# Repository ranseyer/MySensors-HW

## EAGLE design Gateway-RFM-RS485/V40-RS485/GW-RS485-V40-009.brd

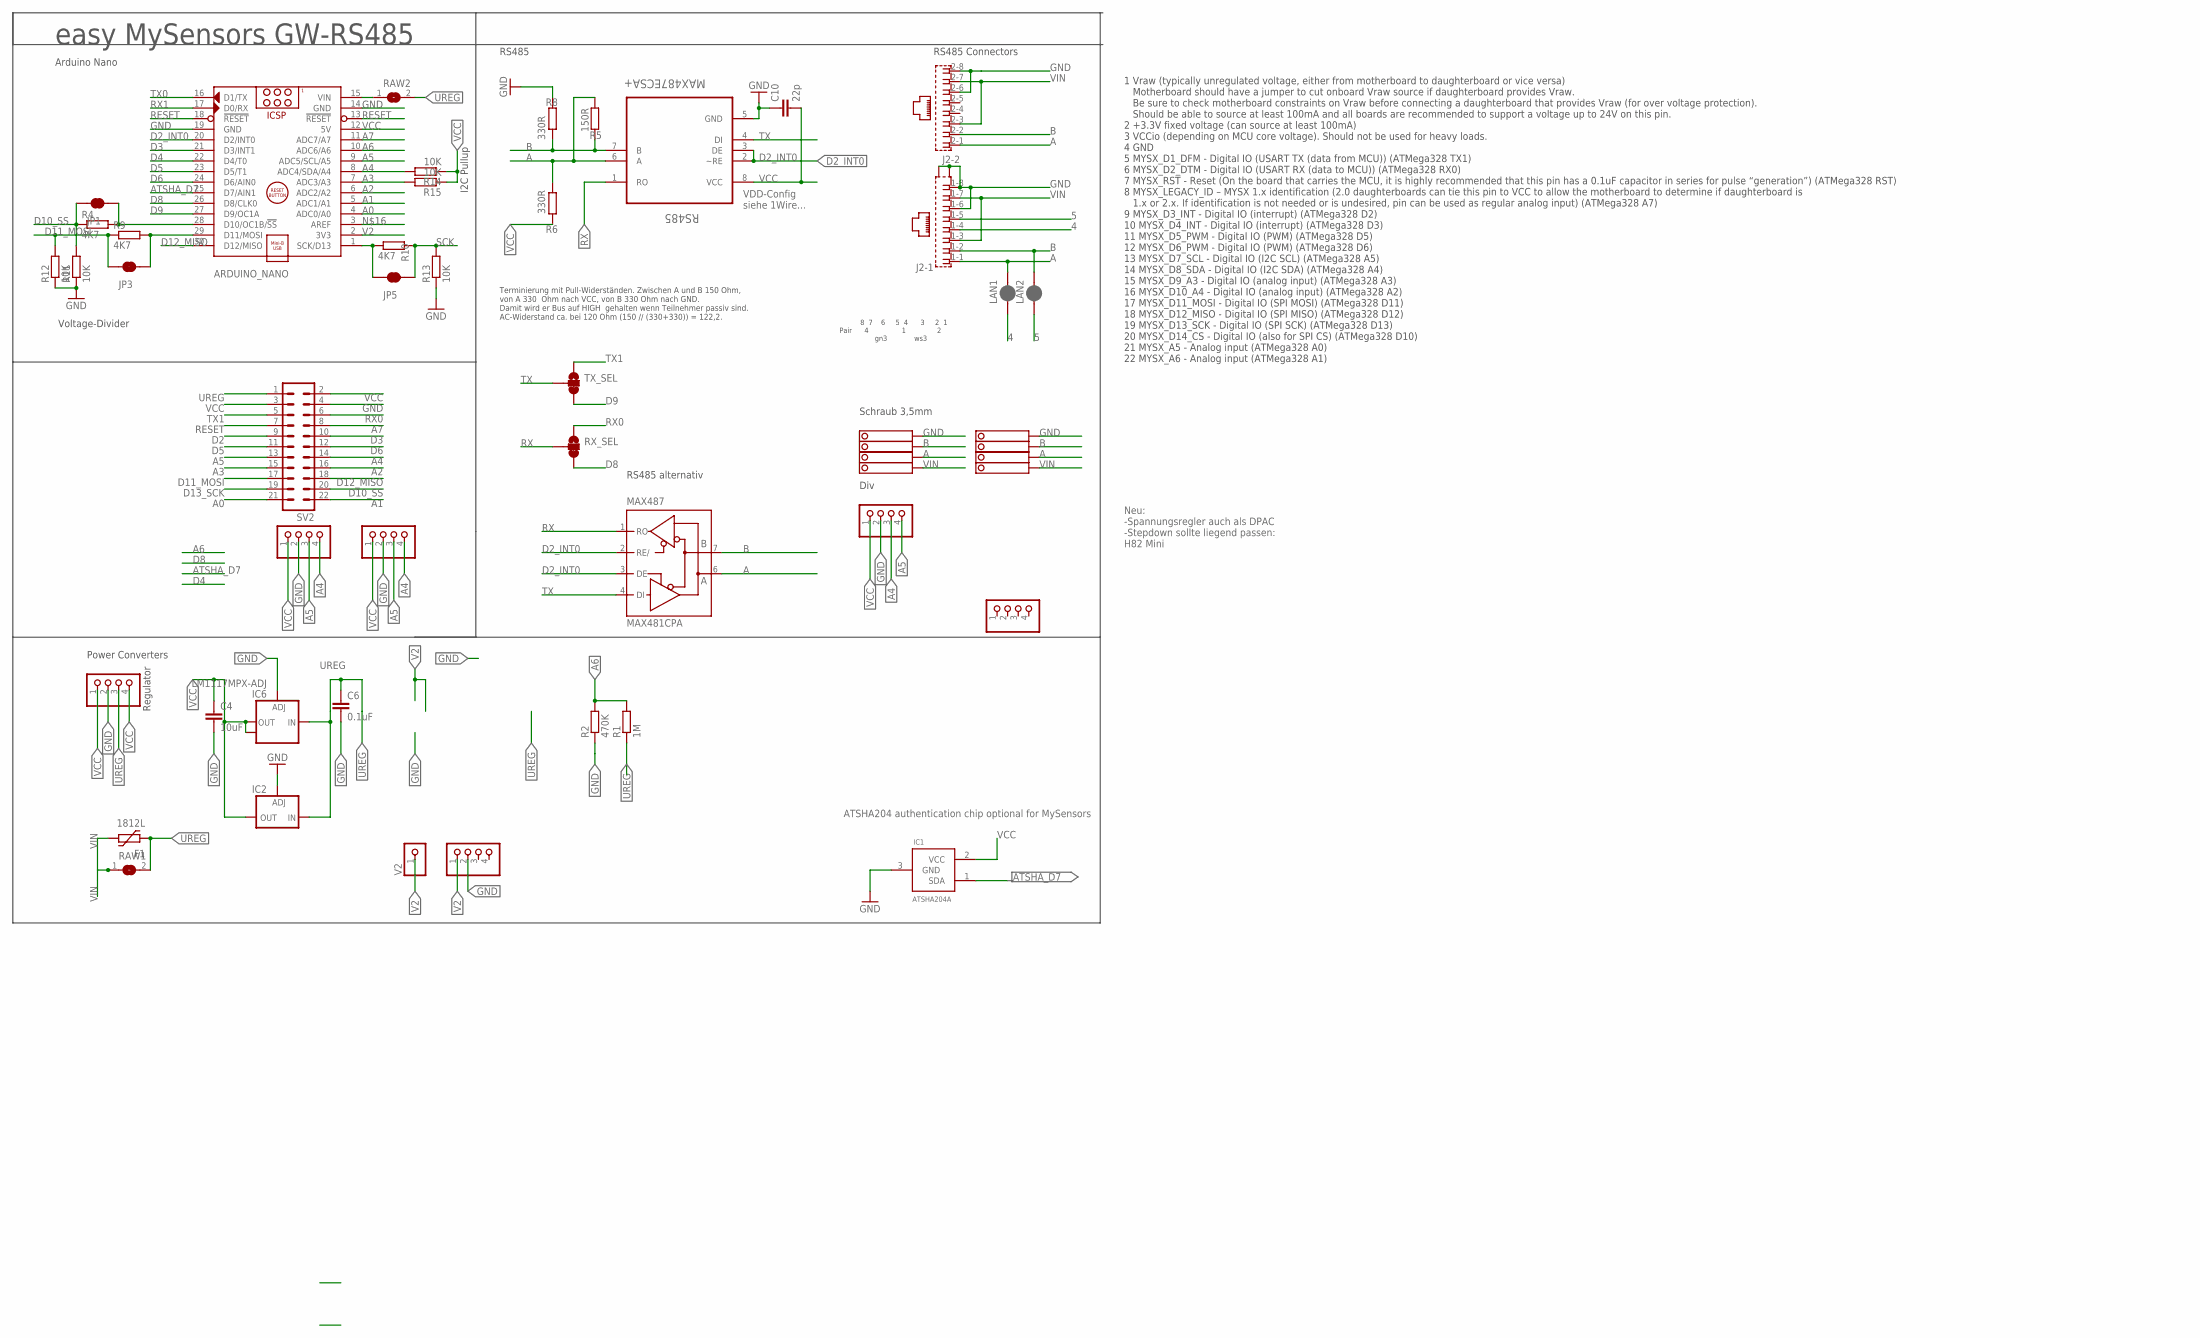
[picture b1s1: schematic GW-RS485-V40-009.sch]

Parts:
ARDUINO_NANO: ARDUINO_NANO_OHNE-BOHR; ARDUINO_NANO
BH1750: PINHD-1X04_2.54-S; 1X04-S
C4: 10uF; C1210
C6: 0.1uF; C1206
C10: 22p; C0805
F1: 1812L
I2C-1, I2C-2: PINHD-1X04_2.54-S; 1X04-S
IC1: ATSHA204A; SOT23
IC2: LD117ADT50TR; DPACK
IC6: LM1117MPX-ADJ; SOT223
J2: RJ45_2X_NARROW_SHILDPINS_NOCASE
JP1, JP3, JP5: JUMPER-SMT_2_NC_TRACE_SILK; SMT-JUMPER_2_NC_TRACE_SILK
JP2: PINHD-1X04_2.54-S; 1X04-S
LAN1, LAN2: JUMPER-SMT_2_NC_PASTE_SILK; SMT-JUMPER_2_NC_PASTE_SILK
MAX487: MAX481CPA; DIL08
R1: 1M; R0805
R2: 470K; R0805
R4, R9, R10: 4K7; M0805
R5: 150R; R0805
R6, R8: 330R; R0805
R11, R12, R13: 10K; M0805
R14, R15: 10K; R0805
RAW1, RAW2: SJ
RS485: MAX487ECSA+; SOIC127P600X175-8N
RX_SEL: JUMPER-SMT_3_1-NC_TRACE_SILK; SMT-JUMPER_3_1-NC_TRACE_SILK
STEPDWN: PINHD-1X04_2.54-S; 1X04-S
SV2: MA11-2
TX_SEL: JUMPER-SMT_3_1-NC_TRACE_SILK; SMT-JUMPER_3_1-NC_TRACE_SILK
V2: PINHD-1X1; 1X01
V2-: PINHD-1X04_2.54-S; 1X04-S
X1, X4: 1751264

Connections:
4: J2.1-4 (4), LAN1.1
5: J2.1-5 (5), LAN2.1
A: J2.1-1 (1), J2.2-1 (1), LAN1.2, MAX487.6 (A), R5.1, R6.2, RS485.6 (A), X1.2, X4.2
A0: ARDUINO_NANO.4 (ADC0/A0), SV2.21
A1: ARDUINO_NANO.5 (ADC1/A1), SV2.22
A2: ARDUINO_NANO.6 (ADC2/A2), SV2.16
A3: ARDUINO_NANO.7 (ADC3/A3), R15.2, SV2.15
A4: ARDUINO_NANO.8 (ADC4/SDA/A4), BH1750.4, I2C-1.4, I2C-2.3, R14.2, SV2.14
A5: ARDUINO_NANO.9 (ADC5/SCL/A5), BH1750.3, I2C-1.3, I2C-2.4, SV2.13
A6: ARDUINO_NANO.10 (ADC6/A6), R1.2, R2.2
A7: ARDUINO_NANO.11 (ADC7/A7), SV2.8
ATSHA_D7: ARDUINO_NANO.25 (D7/AIN1), IC1.1 (SDA)
B: J2.1-2 (2), J2.2-2 (2), LAN2.2, MAX487.7 (B), R5.2, R8.1, RS485.7 (B), X1.3, X4.3
D2: SV2.9
D2_INT0: ARDUINO_NANO.20 (D2/INT0), MAX487.2 (RE/), MAX487.3 (DE), RS485.2 (~RE), RS485.3 (DE)
D3: ARDUINO_NANO.21 (D3/INT1), SV2.10
D4: ARDUINO_NANO.22 (D4/T0)
D5: ARDUINO_NANO.23 (D5/T1), SV2.11
D6: ARDUINO_NANO.24 (D6/AIN0), SV2.12
D8: ARDUINO_NANO.26 (D8/CLK0), RX_SEL.3
D9: ARDUINO_NANO.27 (D9/OC1A), TX_SEL.3
D10_SS: JP1.1, R4.1, R11.2, SV2.20
D11_MOSI: JP3.1, R9.1, R12.2, SV2.17
D12_MISO: ARDUINO_NANO.30 (D12/MISO), SV2.18
D13_SCK: SV2.19
GND: ARDUINO_NANO.14 (GND), ARDUINO_NANO.19 (GND), BH1750.2, C4.2, C6.2, C10.1, I2C-1.2, I2C-2.2, IC1.3 (GND), IC2.1 (ADJ), IC6.1 (ADJ), J2.1-6 (6), J2.1-8 (8), J2.2-6 (6), J2.2-8 (8), J2.G1 (S1), J2.G3 (S2), MAX487.5 (GND), R2.1, R8.2, R11.1, R12.1, R13.1, RS485.5 (GND), STEPDWN.2, SV2.4, V2-.2, X1.4, X4.4
unnamed: ARDUINO_NANO.1 (SCK/D13), JP5.1, R10.1
unnamed: ARDUINO_NANO.28 (D10/OC1B/!SS), JP1.2, R4.2
unnamed: ARDUINO_NANO.29 (D11/MOSI), JP3.2, R9.2
RAW1: ARDUINO_NANO.15 (VIN), RAW2.1
RESET: ARDUINO_NANO.13 (!RESET), ARDUINO_NANO.18 (!RESET), SV2.7
RX: MAX487.1 (RO), RS485.1 (RO), RX_SEL.2
RX0: RX_SEL.1, SV2.6
RX1: ARDUINO_NANO.17 (D0/RX)
SCK: JP5.2, R10.2, R13.2
TX: MAX487.4 (DI), RS485.4 (DI), TX_SEL.2
TX0: ARDUINO_NANO.16 (D1/TX)
TX1: SV2.5, TX_SEL.1
UREG: C6.1, F1.P$1 (1), IC2.3 (IN), IC6.3 (IN), R1.1, RAW1.2, RAW2.2, STEPDWN.3, SV2.1
V2: ARDUINO_NANO.2 (3V3), V2.1, V2-.1
VCC: ARDUINO_NANO.12 (5V), BH1750.1, C4.1, C10.2, I2C-1.1, I2C-2.1, IC1.2 (VCC), IC2.4 (OUT), IC6.2 (OUT), IC6.TAB (OUT1), MAX487.8 (VCC), R6.1, R14.1, R15.1, RS485.8 (VCC), STEPDWN.1, STEPDWN.4, SV2.2, SV2.3
VIN: F1.P$2 (2), J2.1-3 (3), J2.1-7 (7), J2.2-3 (3), J2.2-7 (7), RAW1.1, X1.1, X4.1

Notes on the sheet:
easy MySensors GW-RS485
Arduino Nano
ATSHA204 authentication chip optional for MySensors
Div
Neu: -Spannungsregler auch als DPAC -Stepdown sollte liegend passen: H82 Mini
Power Converters
RS485
VDD-Config siehe 1Wire...
Terminierung mit Pull-Widerständen. Zwischen A und B 150 Ohm, von A 330 Ohm nach VCC, von B 330 Ohm nach GND. Damit wird er Bus auf HIGH gehalten wenn Teilnehmer passiv sind. AC-Widerstand ca. bei 120 Ohm (150 // (330+330)) = 122,2.
Schraub 3,5mm
8 7 6 5 4 3 2 1 Pair 4 1 2 gn3 ws3
Regulator
RS485 Connectors
1 Vraw (typically unregulated voltage, either from motherboard to daughterboard or vice versa) Motherboard should have a jumper to cut onboard Vraw source if daughterboard provides Vraw. Be sure to check motherboard constraints on Vraw before connecting a daughterboard that provides Vraw (for over 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
Voltage-Divider
RS485 alternativ
I2C Pullup

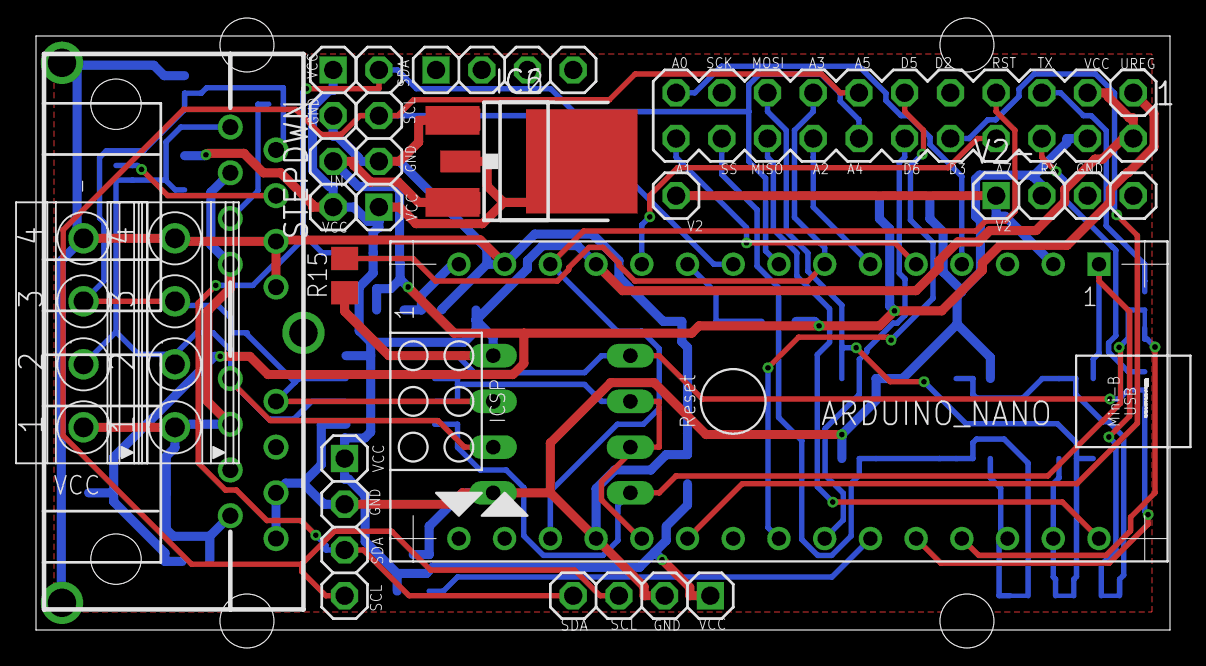
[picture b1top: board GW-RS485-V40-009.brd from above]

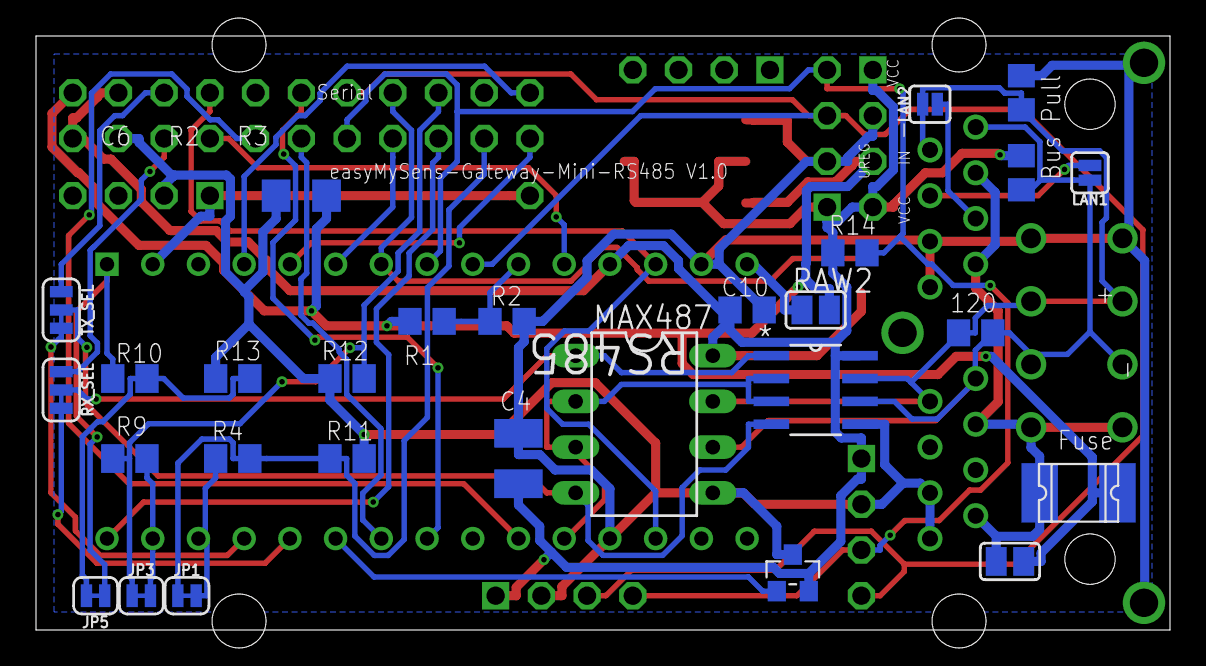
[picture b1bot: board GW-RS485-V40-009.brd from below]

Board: 2 copper layers, 63.0 x 33.0 mm, 43 parts (28 on the bottom side), 37 nets.

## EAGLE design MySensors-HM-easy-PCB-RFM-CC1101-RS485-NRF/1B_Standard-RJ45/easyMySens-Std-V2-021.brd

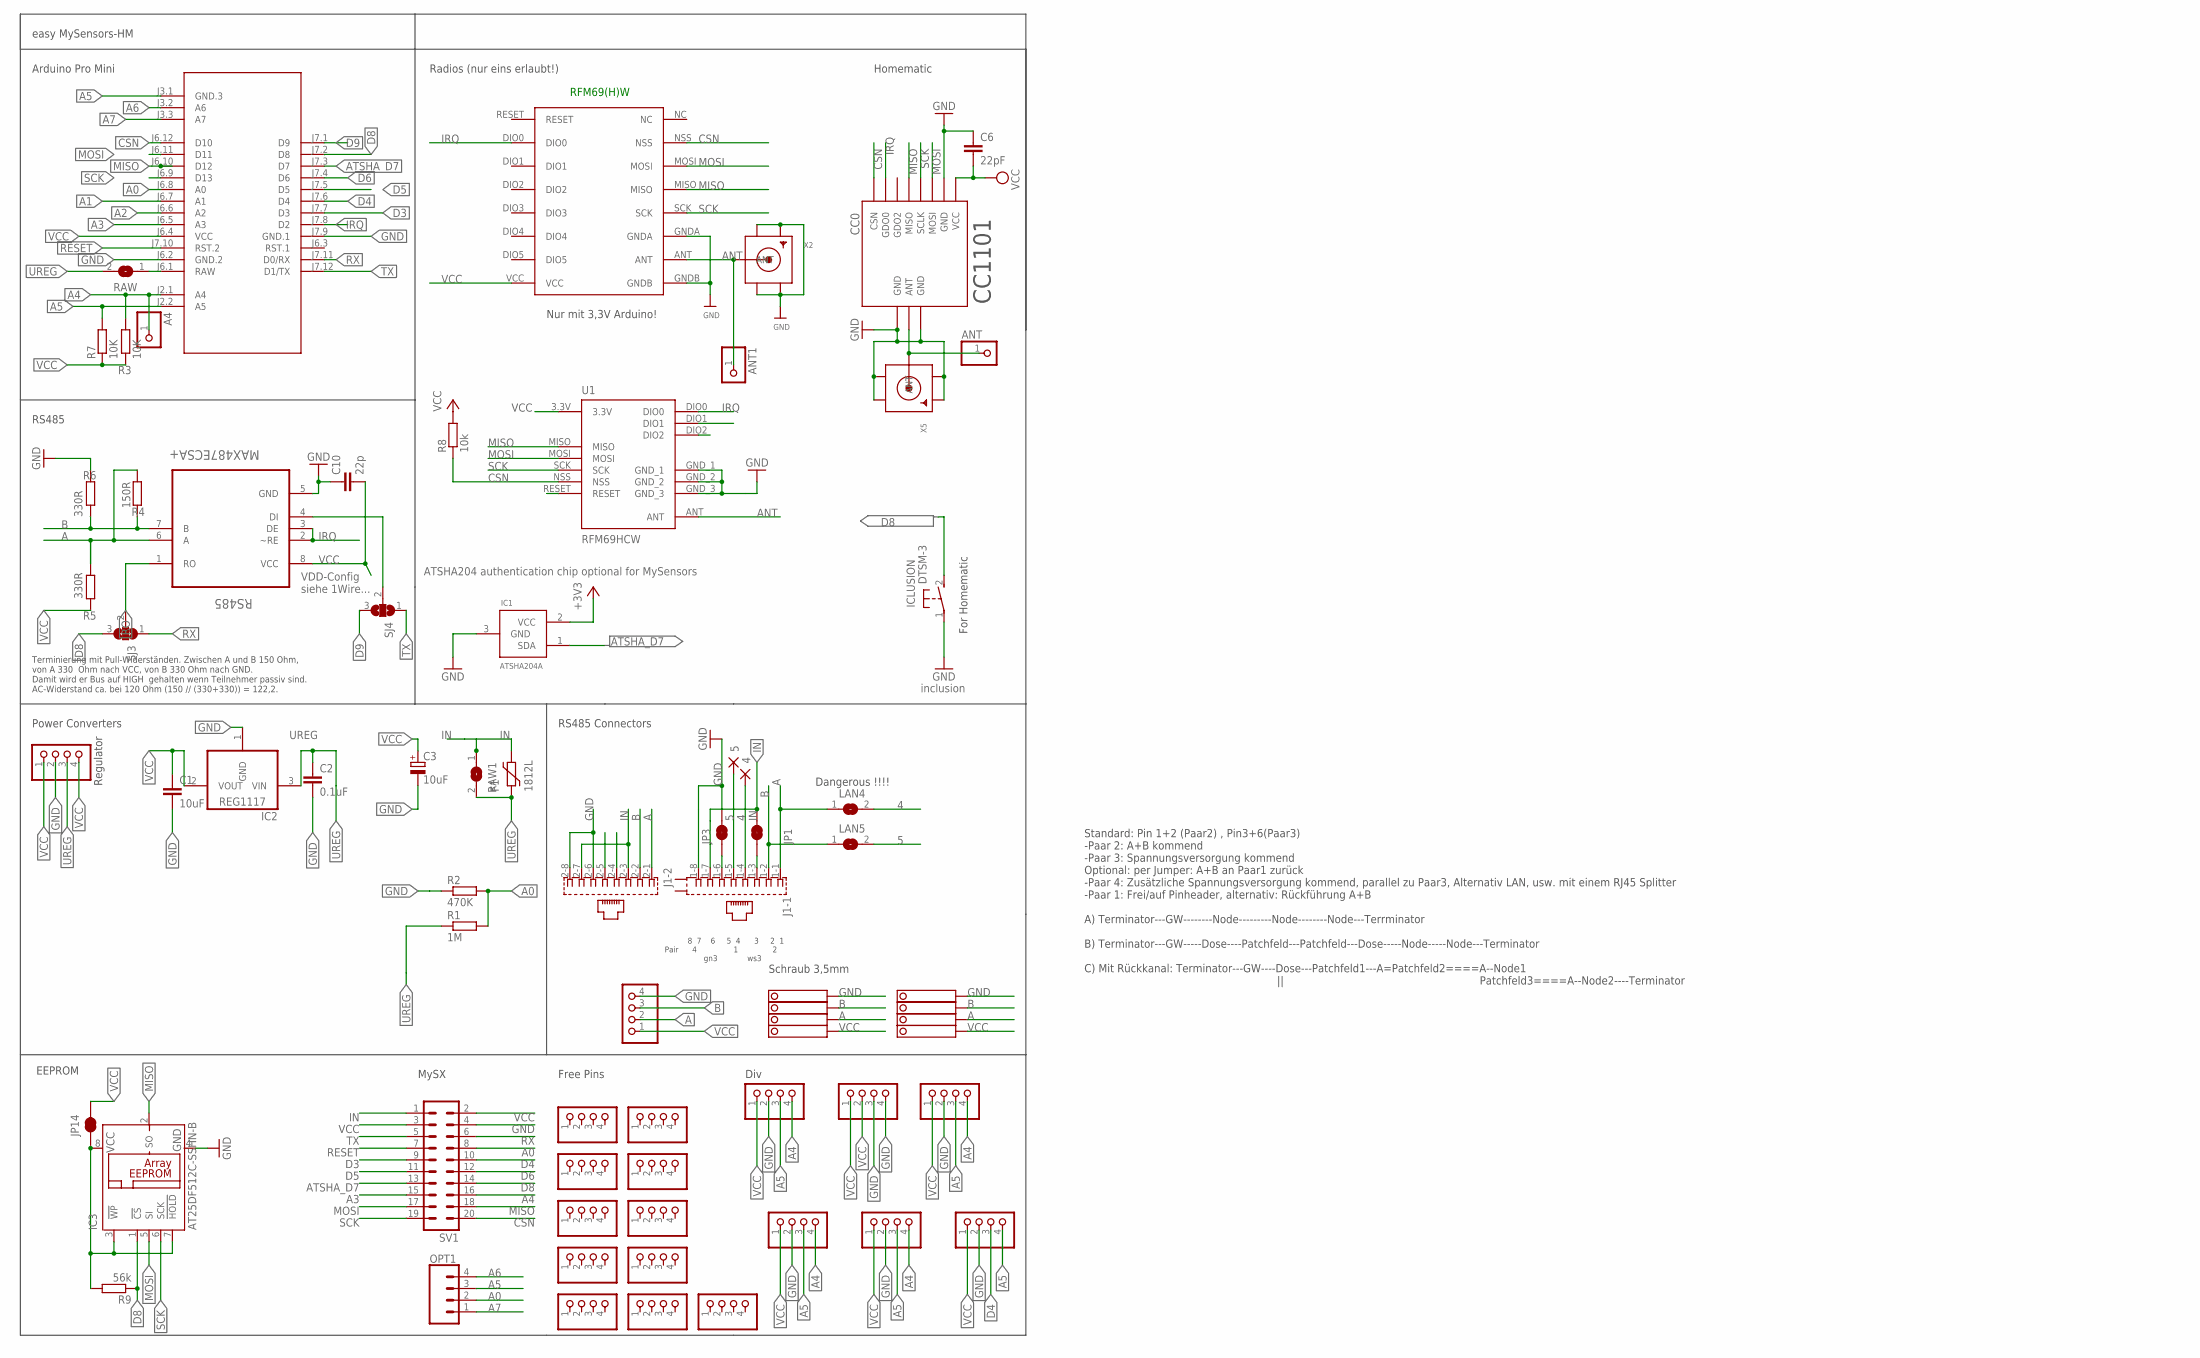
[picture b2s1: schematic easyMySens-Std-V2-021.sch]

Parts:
4, 5: 1,6/0,8
A4: PINHD-1X1; 1X01
ANT, ANT1: PINHD-1X1; 1X01
BH1750: PINHD-1X04_2.54-S; 1X04-S
C1: 10uF; C1210
C2: 0.1uF; C1206
C3: 10uF; SMC_C
C6: 22pF; C0805
C10: 22p; C0805
CC0: CC1101; CC1101_MODULE1_SMD
F1: 1812L
I2C-1, I2C-2, I2C-3, I2C-4: PINHD-1X04_2.54-S; 1X04-S
IC1: ATSHA204A; SOT23
IC2: REG1117; SOT223
IC3: AT25DF512C-SSHN-B; SO-08
ICLUSION: DTSM-3
J1: 557570-1
JP1, JP3, JP14: JUMPER-SMT_2_NC_TRACE_SILK; SMT-JUMPER_2_NC_TRACE_SILK
JP2, JP4, JP5, JP6, JP7, JP8, JP9, JP10, JP11, JP12, JP13: PINHD-1X04_2.54-S; 1X04-S
LAN4, LAN5: SJ
M1: ARDUINO-PRO-MINI-3.3V#NP; ARDUINO-PRO-MINI#NP
MOTION: PINHD-1X04_2.54-S; 1X04-S
OPT1: CONN_04; 1X04
R1: 1M; R0805
R2: 470K; R0805
R3, R7: 10K; R0805
R4: 150R; R0805
R5, R6: 330R; R0805
R8: 10k; M0805
R9: 56k; M0805
RAW, RAW1: SJ
RFM69W: RFM69HW; RFM
RS485: MAX487ECSA+; SOIC127P600X175-8N
RS485-: PINHD-1X04_2.54-S; 1X04-S
SJ3, SJ4: SJ2W; SJ_2
STEPDWN: PINHD-1X04_2.54-S; 1X04-S
SV1: MA10-2
U1: RFM69HCW; RFM69HCW-XXXS2
X1, X4: 1751264
X2, X5: SMACONNECTOR_EDGE; SMA_EDGELAUNCH

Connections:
3: J1.1-3 (3), JP1.1
3.3V: IC1.2 (VCC)
4: 4.1, J1.1-4 (4), LAN4.2
5: 5.1, J1.1-5 (5), LAN5.2
6: J1.1-6 (6), JP3.1
A: J1.1-1 (1), J1.2-1 (1), LAN4.1, R4.1, R5.2, RS485.6 (A), RS485-.2, X1.2, X4.2
A0: M1.J6.8 (A0), OPT1.2, R1.2, R2.2, SV1.8
A1: M1.J6.7 (A1)
A2: M1.J6.6 (A2)
A3: M1.J6.5 (A3), SV1.15
A4: A4.1, BH1750.4, I2C-1.4, I2C-2.4, I2C-4.4, M1.J2.1 (A4), R3.2, SV1.16
A5: BH1750.3, I2C-1.3, I2C-2.3, I2C-4.3, M1.J2.2 (A5), M1.J3.1 (GND.3), MOTION.4, OPT1.3, R7.2
A6: M1.J3.2 (A6), OPT1.4
A7: M1.J3.3 (A7), OPT1.1
ANT: ANT1.1, RFM69W.ANT, U1.ANT, X2.P (ANT)
ANT0: ANT.1, CC0.ANT, X5.P (ANT)
ATSHA_D7: IC1.1 (SDA), M1.J7.3 (D7), SV1.13
B: J1.1-2 (2), J1.2-2 (2), LAN5.1, R4.2, R6.1, RS485.7 (B), RS485-.3, X1.3, X4.3
CSN: CC0.CSN, M1.J6.12 (D10), R8.1, RFM69W.NSS, SV1.20, U1.NSS
D3: M1.J7.7 (D3), SV1.9
D4: M1.J7.6 (D4), MOTION.3, SV1.10
D5: M1.J7.5 (D5), SV1.11
D6: M1.J7.4 (D6), SV1.12
D8: IC3.1 (!CS), ICLUSION.2, M1.J7.2 (D8), R9.1, SJ3.3, SV1.14
D9: M1.J7.1 (D9), SJ4.3
DI1: RS485.4 (DI), SJ4.2
GND: BH1750.2, C1.2, C2.2, C3.-, C6.1, C10.1, CC0.GND@0 (GND), CC0.GND@1 (GND), CC0.GND@2 (GND), I2C-1.2, I2C-2.2, I2C-3.3, I2C-3.4, I2C-4.2, IC1.3 (GND), IC2.1 (GND), IC3.4 (GND), ICLUSION.1, J1.1-8 (8), J1.2-6 (6), J1.2-8 (8), JP3.2, M1.J6.2 (GND.2), M1.J7.9 (GND.1), MOTION.2, R2.1, R6.2, RFM69W.GNDA, RFM69W.GNDB, RS485.5 (GND), RS485-.4, STEPDWN.2, SV1.4, U1.GND_1, U1.GND_2, U1.GND_3, X1.4, X2.GND@1 (GND4), X2.GND@2 (GND3), X2.GND@3 (GND2), X2.GND@4 (GND1), X4.4, X5.GND@1 (GND4), X5.GND@2 (GND3), X5.GND@3 (GND2), X5.GND@4 (GND1)
IN: F1.P$2 (2), J1.1-7 (7), J1.2-3 (3), J1.2-7 (7), JP1.2, RAW1.1, SV1.1
IRQ: CC0.GDO0, M1.J7.8 (D2), RFM69W.DIO0, RS485.2 (~RE), RS485.3 (DE), U1.DIO0
MISO: CC0.MISO, IC3.2 (SO), M1.J6.10 (D12), RFM69W.MISO, SV1.18, U1.MISO
MOSI: CC0.MOSI, IC3.5 (SI), M1.J6.11 (D11), RFM69W.MOSI, SV1.17, U1.MOSI
RAW: M1.J6.1 (RAW), RAW.1
RESET: M1.J7.10 (RST.2), SV1.7
RO: RS485.1 (RO), SJ3.2
RX: M1.J7.11 (D0/RX), SJ3.1, SV1.6
SCK: CC0.SCLK, IC3.6 (SCK), M1.J6.9 (D13), RFM69W.SCK, SV1.19, U1.SCK
TX: M1.J7.12 (D1/TX), SJ4.1, SV1.5
UREG: C2.1, F1.P$1 (1), IC2.3 (VIN), R1.1, RAW.2, RAW1.2, STEPDWN.3
VCC: BH1750.1, C1.1, C3.+, C6.2, C10.2, CC0.VCC, I2C-1.1, I2C-2.1, I2C-3.1, I2C-3.2, I2C-4.1, IC2.2 (VOUT), JP14.2, M1.J6.4 (VCC), MOTION.1, R3.1, R5.1, R7.1, R8.2, RFM69W.VCC, RS485.8 (VCC), RS485-.1, STEPDWN.1, STEPDWN.4, SV1.2, SV1.3, U1.3.3V, X1.1, X4.1
VCC1: IC3.3 (!WP), IC3.7 (!HOLD), IC3.8 (VCC), JP14.1, R9.2

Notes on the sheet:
easy MySensors-HM
Arduino Pro Mini
Free Pins
Power Converters
RS485
VDD-Config siehe 1Wire...
ATSHA204 authentication chip optional for MySensors
RFM69(H)W
Nur mit 3,3V Arduino!
CC1101
Terminierung mit Pull-Widerständen. Zwischen A und B 150 Ohm, von A 330 Ohm nach VCC, von B 330 Ohm nach GND. Damit wird er Bus auf HIGH gehalten wenn Teilnehmer passiv sind. AC-Widerstand ca. bei 120 Ohm (150 // (330+330)) = 122,2.
Schraub 3,5mm
Div
Radios (nur eins erlaubt!)
inclusion
8 7 6 5 4 3 2 1 Pair 4 1 2 gn3 ws3
Standard: Pin 1+2 (Paar2) , Pin3+6(Paar3) -Paar 2: A+B kommend -Paar 3: Spannungsversorgung kommend Optional: per Jumper: A+B an Paar1 zurück -Paar 4: Zusätzliche Spannungsversorgung kommend, parallel zu Paar3, Alternativ LAN, usw. mit einem RJ45 Splitter -Paar 1: Frei/auf Pinheader, alternativ: Rü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
Dangerous !!!!
Regulator
For Homematic
RS485 Connectors
Homematic
EEPROM
MySX

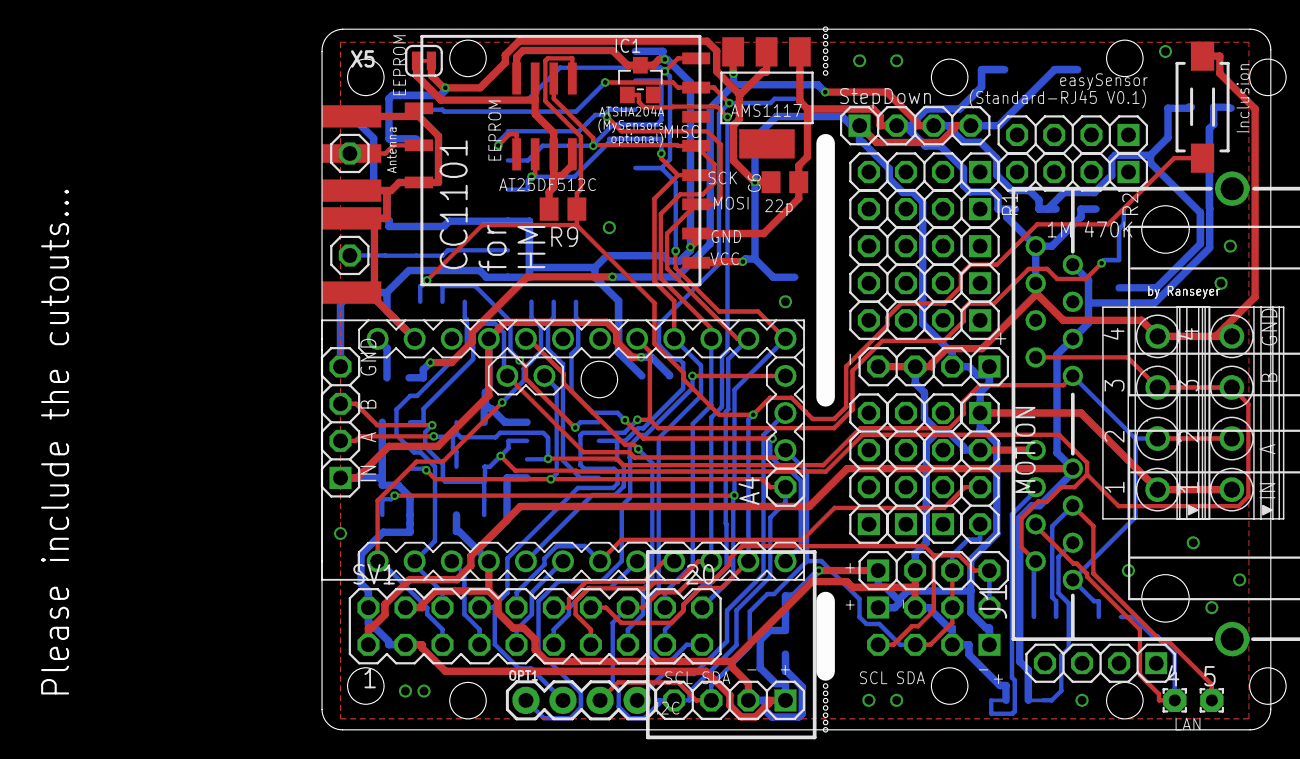
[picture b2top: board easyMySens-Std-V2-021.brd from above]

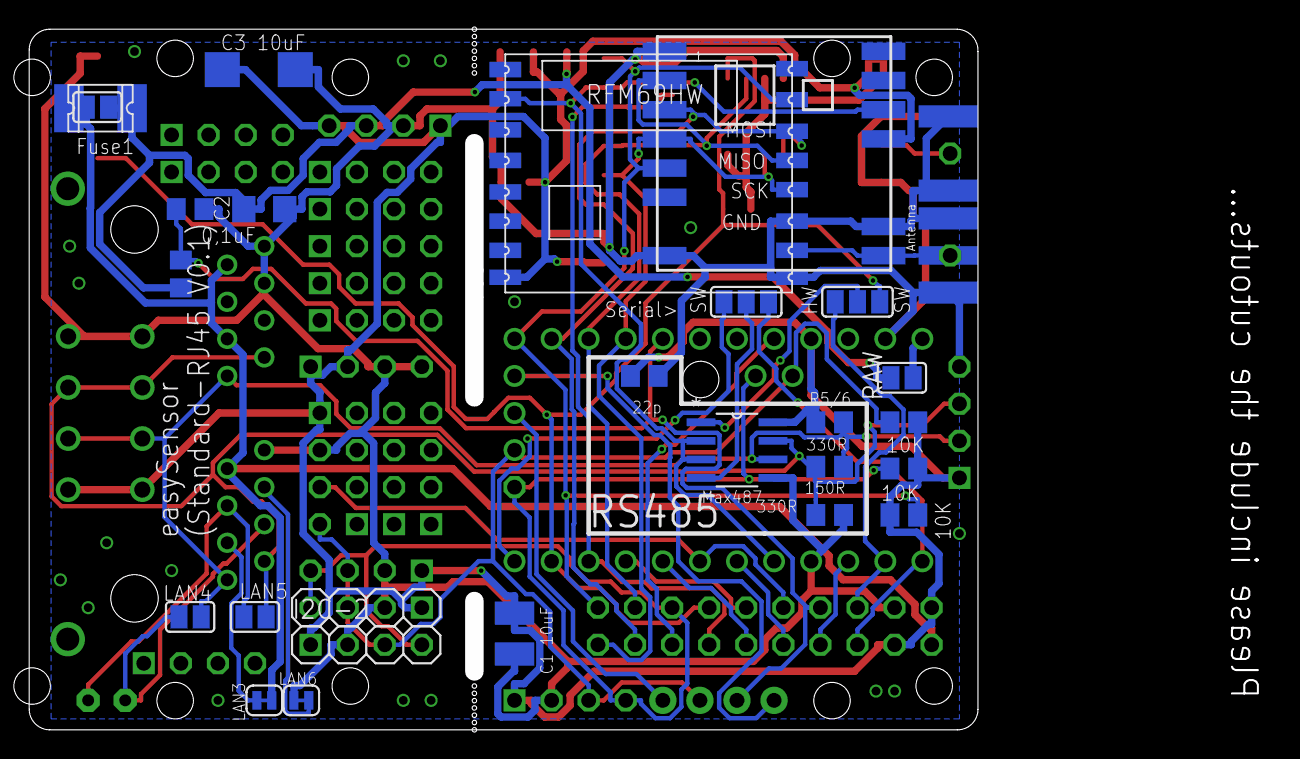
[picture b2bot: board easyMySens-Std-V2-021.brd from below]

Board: 2 copper layers, 65.0 x 48.0 mm, 64 parts (27 on the bottom side), 37 nets.

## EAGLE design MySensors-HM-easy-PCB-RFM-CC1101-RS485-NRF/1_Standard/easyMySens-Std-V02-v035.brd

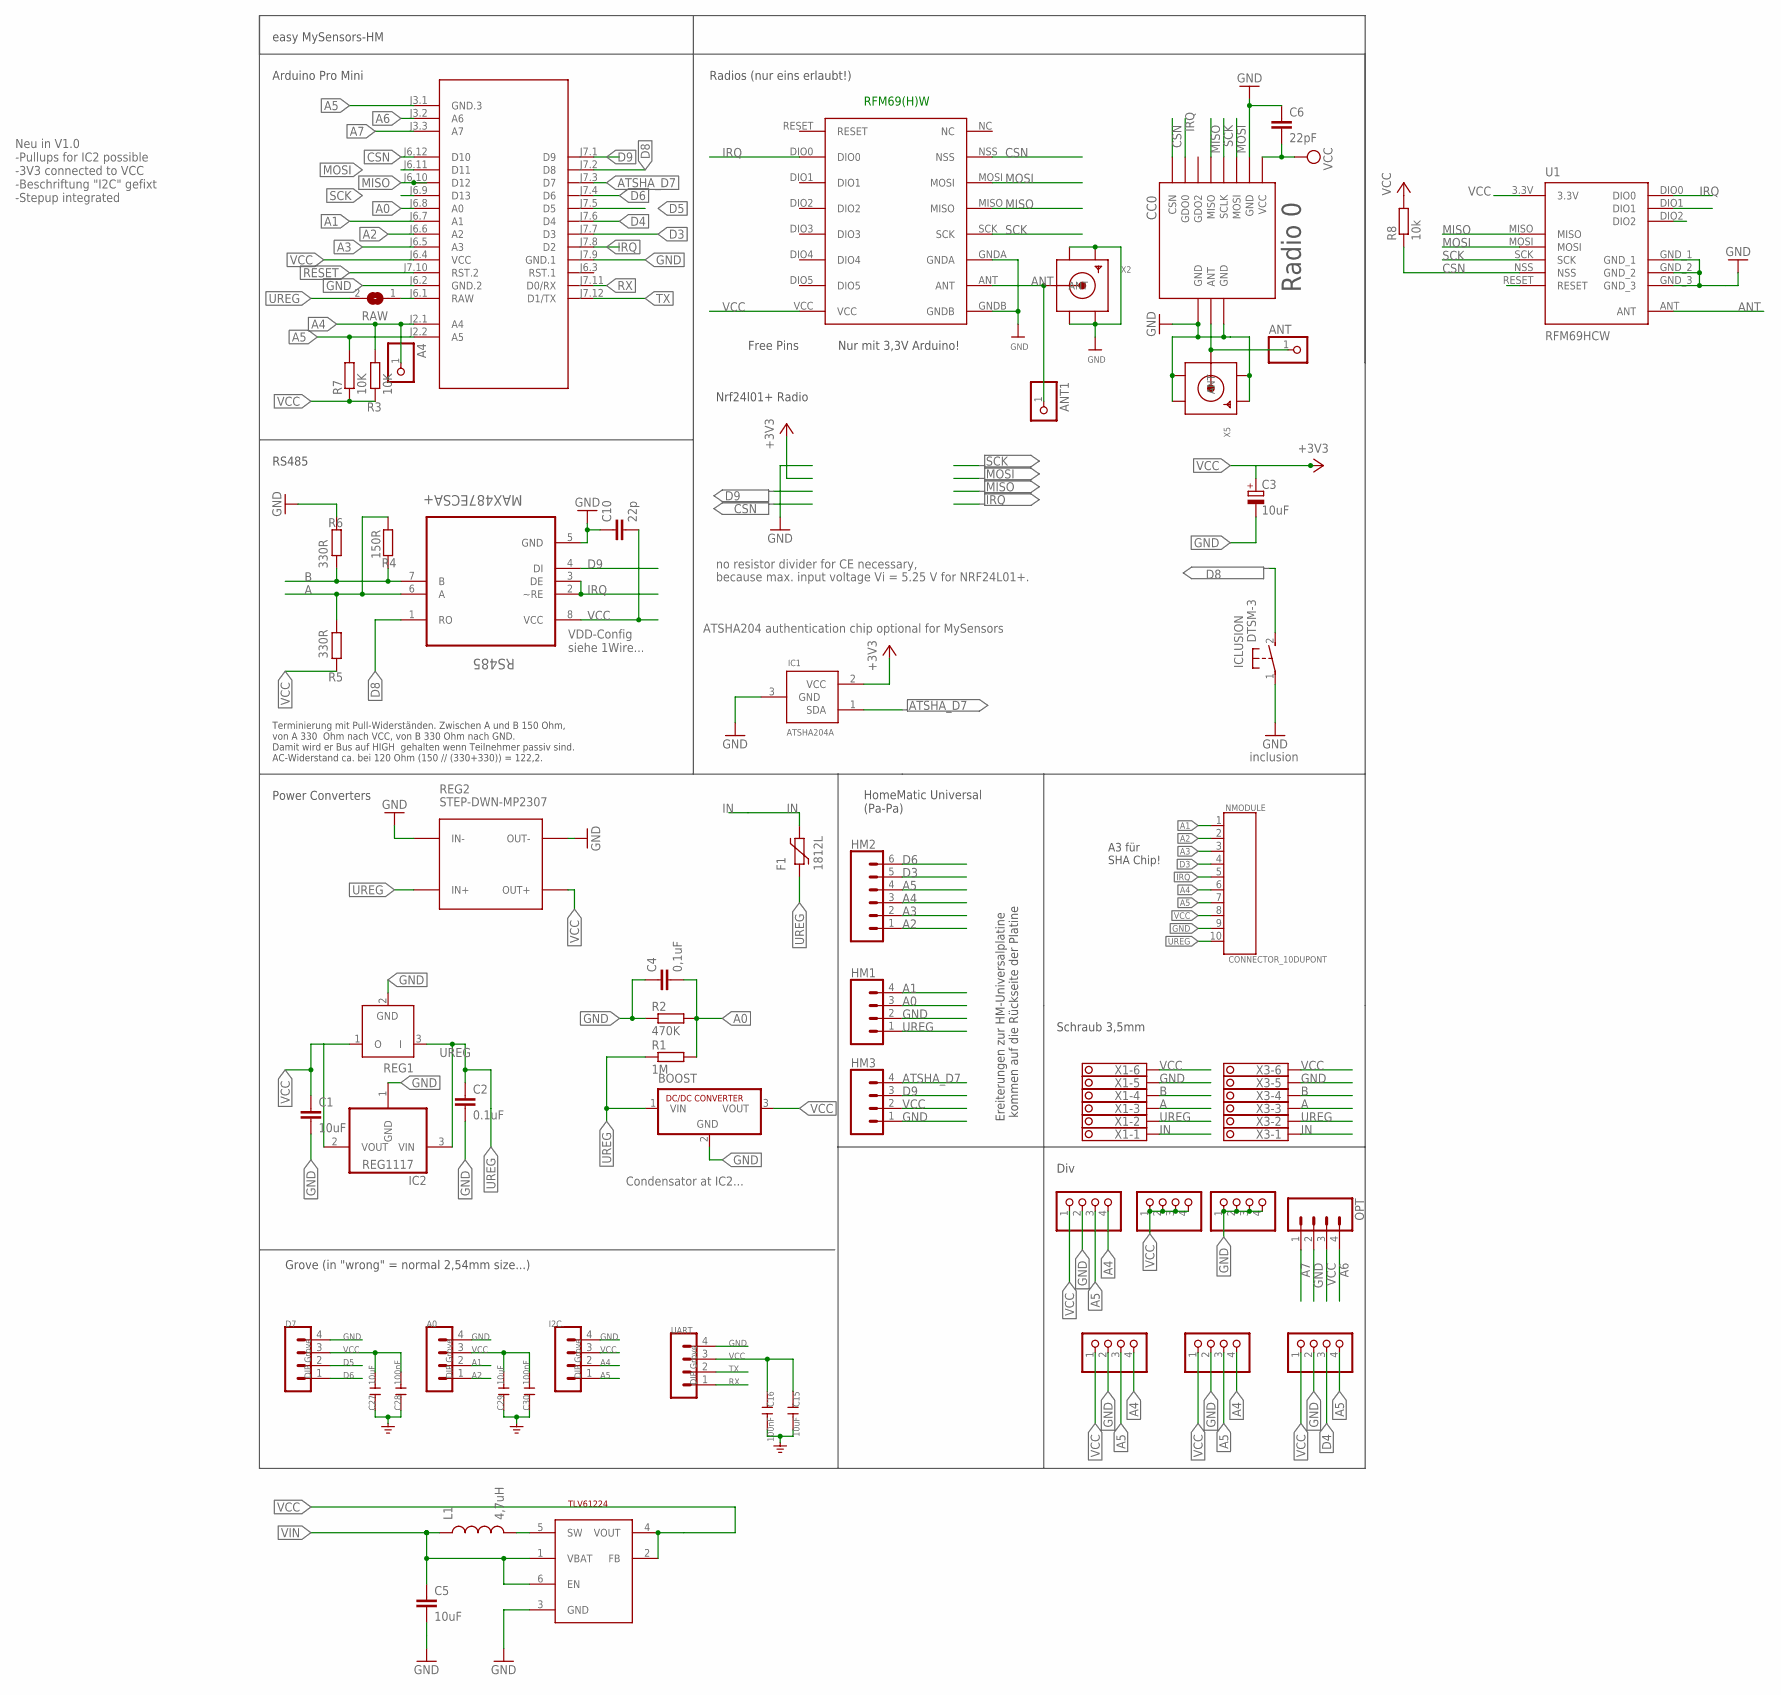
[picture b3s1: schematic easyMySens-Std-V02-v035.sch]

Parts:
A0: DIP Grove; MA04-1
A4: PINHD-1X1; 1X01
ANT, ANT1: PINHD-1X1; 1X01
BH1750: PINHD-1X04_2.54-S; 1X04-S
BOOST: R-78C1.8-1.0; SIP3
C1: 10uF; C1210
C2: 0.1uF; C1206
C3: 10uF; SMC_C
C4: 0,1uF; C1206
C5: 10uF; 0805
C6: 22pF; C0805
C10: 22p; C0805
C15, C27, C29: 10uF; C0603
C16, C28, C30: 100nF; C0603
CC0: CC1101; CC1101_MODULE1_SMD
D7: DIP Grove; MA04-1
F1: 1812L
HM1, HM3: CONN_04; 1X04
HM2: CONN_06SILK_FEMALE_PTH; 1X06
I2C-1, I2C-2: PINHD-1X04_2.54-S; 1X04-S
I2C.: DIP Grove; MA04-1
IC1: ATSHA204A; SOT23
IC2: REG1117; SOT223
ICLUSION: DTSM-3
JP1, JP3: PINHD-1X04_2.54-S; 1X04-S
L1: 4,7uH; 0805
M1: ARDUINO-PRO-MINI-3.3V#NP; ARDUINO-PRO-MINI#NP
MOTION: PINHD-1X04_2.54-S; 1X04-S
NMODULE: CONNECTOR_10DUPONT; DUPONT_10
OPT: CONN_04; 1X04
R1: 1M; R0805
R2: 470K; R0805
R3, R7: 10K; R0805
R4: 150R; R0805
R5, R6: 330R; R0805
R8: 10k; M0805
RAW: SJ
REG1: LP2950Z; TO92
REG2: STEP-DWN-MP2307; DC-DC-STEP-DOWN-MP2307
RFM69W: RFM69HW; RFM
RS485: MAX487ECSA+; SOIC127P600X175-8N
STEPUP: TLV61224; SOT23-6L
U1: RFM69HCW; RFM69HCW-XXXS2
UART: DIP Grove; MA04-1
X1, X3: 1751280
X2, X5: SMACONNECTOR_EDGE; SMA_EDGELAUNCH

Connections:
3.3V: IC1.2 (VCC)
A: R4.1, R5.2, RS485.6 (A), X1.3, X3.3
A0: C4.2, HM1.3, M1.J6.8 (A0), R1.2, R2.2
A1: A0.2, HM1.4, M1.J6.7 (A1), NMODULE.1
A2: A0.1, HM2.1, M1.J6.6 (A2), NMODULE.2
A3: HM2.2, M1.J6.5 (A3), NMODULE.3
A4: A4.1, BH1750.4, HM2.3, I2C-1.4, I2C-2.4, I2C..2, M1.J2.1 (A4), NMODULE.6, R3.2
A5: BH1750.3, HM2.4, I2C-1.3, I2C-2.3, I2C..1, M1.J2.2 (A5), M1.J3.1 (GND.3), MOTION.4, NMODULE.7, R7.2
A6: M1.J3.2 (A6), OPT.4
A7: M1.J3.3 (A7), OPT.1
ANT: ANT1.1, RFM69W.ANT, U1.ANT, X2.P (ANT)
ANT0: ANT.1, CC0.ANT, X5.P (ANT)
ATSHA_D7: HM3.4, IC1.1 (SDA), M1.J7.3 (D7)
B: R4.2, R6.1, RS485.7 (B), X1.4, X3.4
CSN: CC0.CSN, M1.J6.12 (D10), R8.1, RFM69W.NSS, U1.NSS
D3: HM2.5, M1.J7.7 (D3), NMODULE.4
D4: M1.J7.6 (D4), MOTION.3
D5: D7.2, M1.J7.5 (D5)
D6: D7.1, HM2.6, M1.J7.4 (D6)
D8: ICLUSION.2, M1.J7.2 (D8), RS485.1 (RO)
D9: HM3.3, M1.J7.1 (D9), RS485.4 (DI)
GND: A0.4, BH1750.2, BOOST.2 (GND), C1.2, C2.2, C3.-, C4.1, C5.2, C6.1, C10.1, C15.1, C16.1, C27.2, C28.2, C29.2, C30.2, CC0.GND@0 (GND), CC0.GND@1 (GND), CC0.GND@2 (GND), D7.4, HM1.2, HM3.1, I2C-1.2, I2C-2.2, I2C..4, IC1.3 (GND), IC2.1 (GND), ICLUSION.1, JP1.1, JP1.2, JP1.3, JP1.4, M1.J6.2 (GND.2), M1.J7.9 (GND.1), MOTION.2, NMODULE.9, OPT.2, R2.1, R6.2, REG1.2 (GND), REG2.IN-, REG2.OUT-, RFM69W.GNDA, RFM69W.GNDB, RS485.5 (GND), STEPUP.3 (GND), U1.GND_1, U1.GND_2, U1.GND_3, UART.4, X1.5, X2.GND@1 (GND4), X2.GND@2 (GND3), X2.GND@3 (GND2), X2.GND@4 (GND1), X3.5, X5.GND@1 (GND4), X5.GND@2 (GND3), X5.GND@3 (GND2), X5.GND@4 (GND1)
IN: F1.P$2 (2), X1.1, X3.1
IRQ: CC0.GDO0, M1.J7.8 (D2), NMODULE.5, RFM69W.DIO0, RS485.2 (~RE), RS485.3 (DE), U1.DIO0
MISO: CC0.MISO, M1.J6.10 (D12), RFM69W.MISO, U1.MISO
MOSI: CC0.MOSI, M1.J6.11 (D11), RFM69W.MOSI, U1.MOSI
unnamed: L1.2, STEPUP.5 (SW)
RAW: M1.J6.1 (RAW), RAW.1
RESET: M1.J7.10 (RST.2)
RX: M1.J7.11 (D0/RX), UART.1
SCK: CC0.SCLK, M1.J6.9 (D13), RFM69W.SCK, U1.SCK
TX: M1.J7.12 (D1/TX), UART.2
UREG: BOOST.1 (VIN), C2.1, F1.P$1 (1), HM1.1, IC2.3 (VIN), NMODULE.10, R1.1, RAW.2, REG1.3 (I), REG2.IN+, X1.2, X3.2
VCC: A0.3, BH1750.1, BOOST.3 (VOUT), C1.1, C3.+, C6.2, C10.2, C15.2, C16.2, C27.1, C28.1, C29.1, C30.1, CC0.VCC, D7.3, HM3.2, I2C-1.1, I2C-2.1, I2C..3, IC2.2 (VOUT), JP3.1, JP3.2, JP3.3, JP3.4, M1.J6.4 (VCC), MOTION.1, NMODULE.8, OPT.3, R3.1, R5.1, R7.1, R8.2, REG1.1 (O), REG2.OUT+, RFM69W.VCC, RS485.8 (VCC), STEPUP.2 (FB), STEPUP.4 (VOUT), U1.3.3V, UART.3, X1.6, X3.6
VIN: C5.1, L1.1, STEPUP.1 (VBAT), STEPUP.6 (EN)

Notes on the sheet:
easy MySensors-HM
Arduino Pro Mini
Free Pins
Nrf24l01+ Radio
Power Converters
RS485
VDD-Config siehe 1Wire...
no resistor divider for CE necessary,
because max. input voltage Vi = 5.25 V for NRF24L01+.
ATSHA204 authentication chip optional for MySensors
RFM69(H)W
Nur mit 3,3V Arduino!
Radio 0
Terminierung mit Pull-Widerständen. Zwischen A und B 150 Ohm, von A 330 Ohm nach VCC, von B 330 Ohm nach GND. Damit wird er Bus auf HIGH gehalten wenn Teilnehmer passiv sind. AC-Widerstand ca. bei 120 Ohm (150 // (330+330)) = 122,2.
A3 für SHA Chip!
Ereiterungen zur HM-Universalplatine kommen auf die Rückseite der Platine
Condensator at IC2...
HomeMatic Universal (Pa-Pa)
Schraub 3,5mm
Div
Radios (nur eins erlaubt!)
Grove (in "wrong" = normal 2,54mm size...)
Neu in V1.0 -Pullups for IC2 possible -3V3 connected to VCC -Beschriftung "I2C" gefixt -Stepup integrated
inclusion

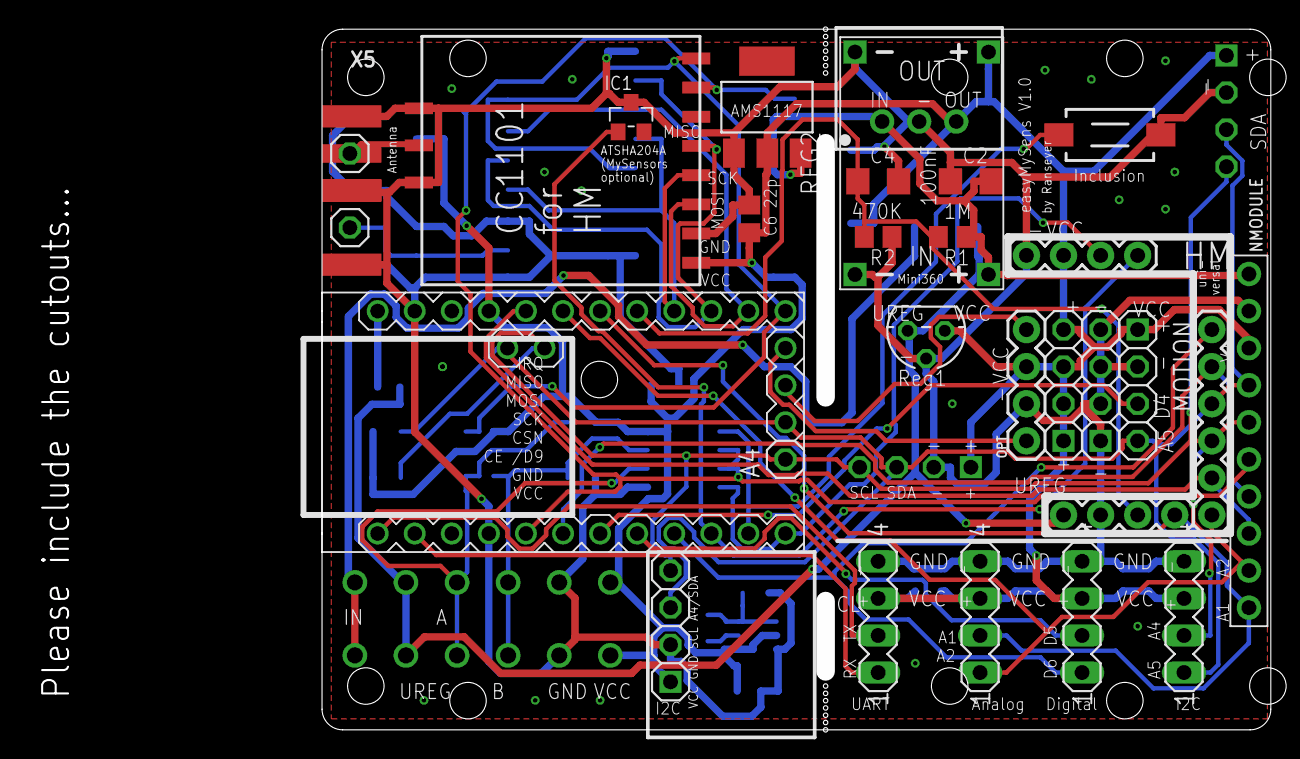
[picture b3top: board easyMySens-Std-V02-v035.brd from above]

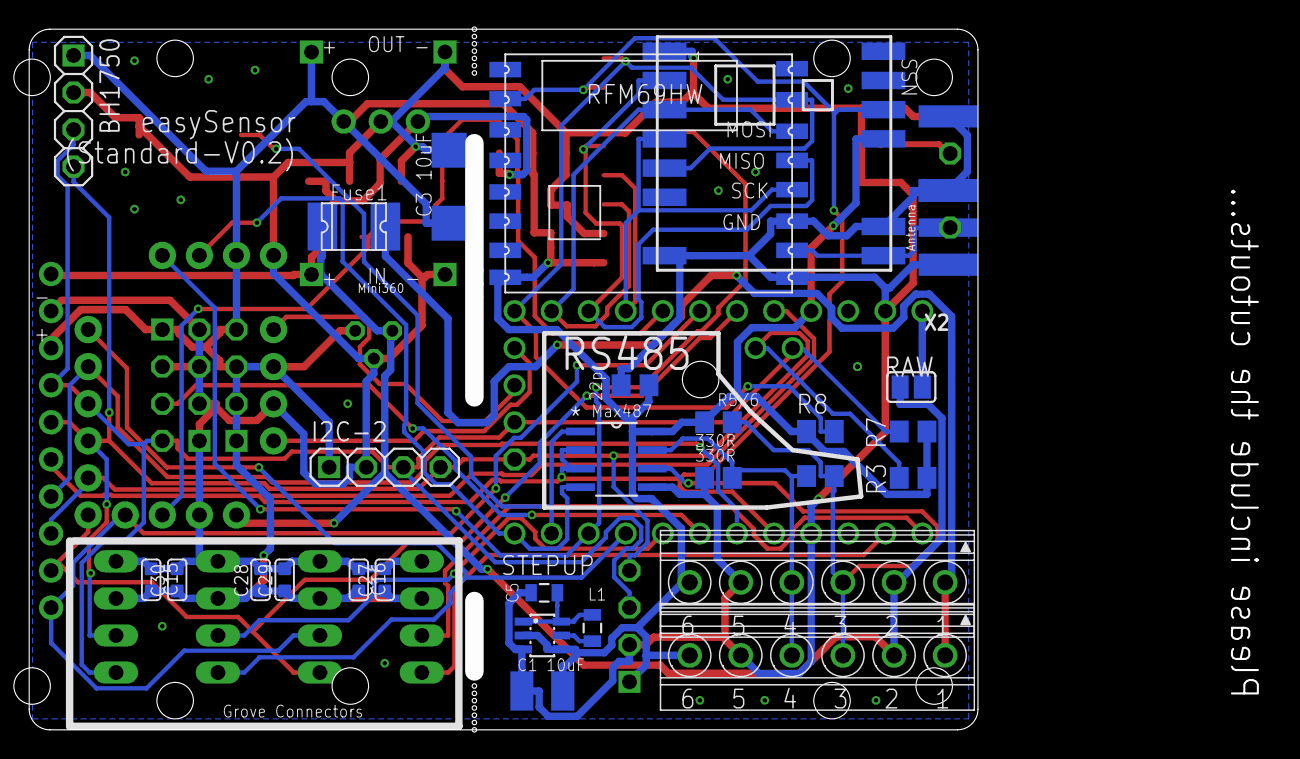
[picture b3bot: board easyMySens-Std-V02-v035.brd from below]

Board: 2 copper layers, 65.0 x 48.0 mm, 58 parts (28 on the bottom side), 33 nets.

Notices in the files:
parts and their libraries:
SparkFun-Jumpers: Licensing: Creative Commons ShareAlike 4.0 International - https://creativecommons.org/licenses/by-sa/4.0
diy-modules: Released under the Creative Commons Attribution 4.0 International License: http://creativecommons.org/licenses/by/4.0
